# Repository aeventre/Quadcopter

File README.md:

# DIY Quadcopter

A from-scratch DIY quadcopter with a custom-designed flight computer PCB and custom frame CAD. Everything except the ESC and radio module was built from the ground up.

## Overview

This repository contains the KiCad hardware design files for the custom flight controller PCB and the Arduino/PlatformIO firmware that runs on it. The flight controller interfaces a four channel off-the-shelf ESC, an RC receiver via CRSF/ExpressLRS, and an onboard 6-axis IMU to stabilize and control the drone.

## Hardware

### Flight Controller (Custom PCB)

| Component | Part | Role |
|---|---|---|
| MCU | Raspberry Pi Pico (RP2040 / RP2350) | Main processor |
| IMU | LSM6DSO32TR | 6-axis accelerometer + gyroscope (SPI) |
| Power regulator | TPS563200 | 3A synchronous step-down, 4.5–17V in → 3.3V |
| Motor switching | AO3400A MOSFET | N-channel switching |
| Level shifting | BSS138 MOSFET | 3.3V ↔ 5V logic |
| Transient protection | SMAJ14A TVS diode | Input voltage spike protection |

### Interfaces
- **4× ESC connectors** (Motor 1–4) — off-the-shelf 4 channel ESC
- **RC receiver connector** — CRSF/ExpressLRS
- **Electromagnet connector** — payload drop mechanism
- **SPI** — IMU (LSM6DSO32TR on SPI1)
- **USB** — programming and debug via Pico's onboard USB

### Frame & CAD
Custom-designed from scratch (CAD files not included in this repo).

## Firmware

Built with [PlatformIO](https://platformio.org/) targeting the Raspberry Pi Pico using the [earlephilhower Arduino core](https://github.com/earlephilhower/arduino-pico).

### Flight Controller (`Code/Controller_Code/`)

The main flight firmware. Initializes the IMU, ESCs, and CRSF receiver, then runs the control loop.

**Libraries (`lib/`)**

| Library | Description |
|---|---|
| `DroneController` | Core flight controller — PID loop, flight modes, arm/disarm, RAM blackbox |
| `ImuLSM6` | SPI driver for the LSM6DSO32TR (gyro + accel reads) |
| `MotorLib` | PWM motor control via the Servo library (1000–2000 µs) |

**Flight modes**

- **Acro** — pure rate mode; stick input maps directly to roll/pitch/yaw rate setpoints fed into the inner PID loop
- **Balance** — self-leveling; an outer angle P+I loop computes rate setpoints from stick-commanded angles, which the inner rate PID tracks

**Control loop**

```
RC input (CRSF)
    │
    ├─ [Balance mode] Angle P+I → rate setpoint
    │
    └─ Rate PID (roll / pitch / yaw)
           │   gyro LP filter (α = 0.70)
           │   complementary filter for attitude (α = 0.98)
           ▼
       Motor mixer → 4× PWM ESC outputs
```

**RAM blackbox**

Up to 3000 samples are logged to RAM during flight (timestamp, RC inputs, rate commands, gyro rates, PID outputs, motor values, attitude angles). On disarm the log dumps over USB serial as CSV for offline analysis.

### Test Projects

| Project | Description |
|---|---|
| `Code/ELRS_Test/` | Standalone CRSF/ExpressLRS receiver test |
| `Code/ESC_Test/` | ESC test using DShot600 (bit-banged on Pico's second core at 2 kHz) |
| `Code/IMU_test/` | Standalone LSM6DSO32TR read/print test |

### Flight Analysis (`Code/Flight_Analysis/`)

MATLAB script (`PID_Analysis.m`) for post-flight analysis of blackbox CSV logs. Plots RC inputs, commanded vs. measured rates, rate errors, motor outputs, and estimated attitude. 103 flight logs are included.

## Repository Structure

```
Quadcopter/
├── Flight_Controller/
│   ├── Flight_Controller.kicad_pro
│   ├── Flight_Controller.kicad_sch
│   └── Flight_Controller.kicad_pcb
└── Code/
    ├── Controller_Code/          # Main flight firmware (PlatformIO)
    │   ├── src/main.cpp
    │   ├── lib/
    │   │   ├── DroneController/  # Flight controller, PID, blackbox
    │   │   ├── ImuLSM6/          # LSM6DSO32TR SPI driver
    │   │   └── MotorLib/         # PWM ESC control
    │   └── Tests/                # Component test sketches
    ├── ELRS_Test/                # ExpressLRS receiver test
    ├── ESC_Test/                 # DShot600 ESC test
    │   └── lib/DshotLib/         # DShot600 driver (dual-core)
    ├── IMU_test/                 # IMU read test
    └── Flight_Analysis/
        ├── PID_Analysis.m        # MATLAB blackbox analysis script
        └── flight_log_*.csv      # Captured flight logs (103 flights)
```

## Getting Started

### Hardware (KiCad)
1. Install [KiCad 7.x or later](https://www.kicad.org/download/)
2. Clone this repository:
   ```bash
   git clone https://github.com/alecv2211/Quadcopter.git
   ```
3. Open `Flight_Controller/Flight_Controller.kicad_pro`

### Firmware (PlatformIO)
1. Install [PlatformIO](https://platformio.org/install)
2. Open `Code/Controller_Code/` in VS Code with the PlatformIO extension
3. Connect the Pico via USB and run **Upload**

## License

Licensed under the [Apache License 2.0](LICENSE).

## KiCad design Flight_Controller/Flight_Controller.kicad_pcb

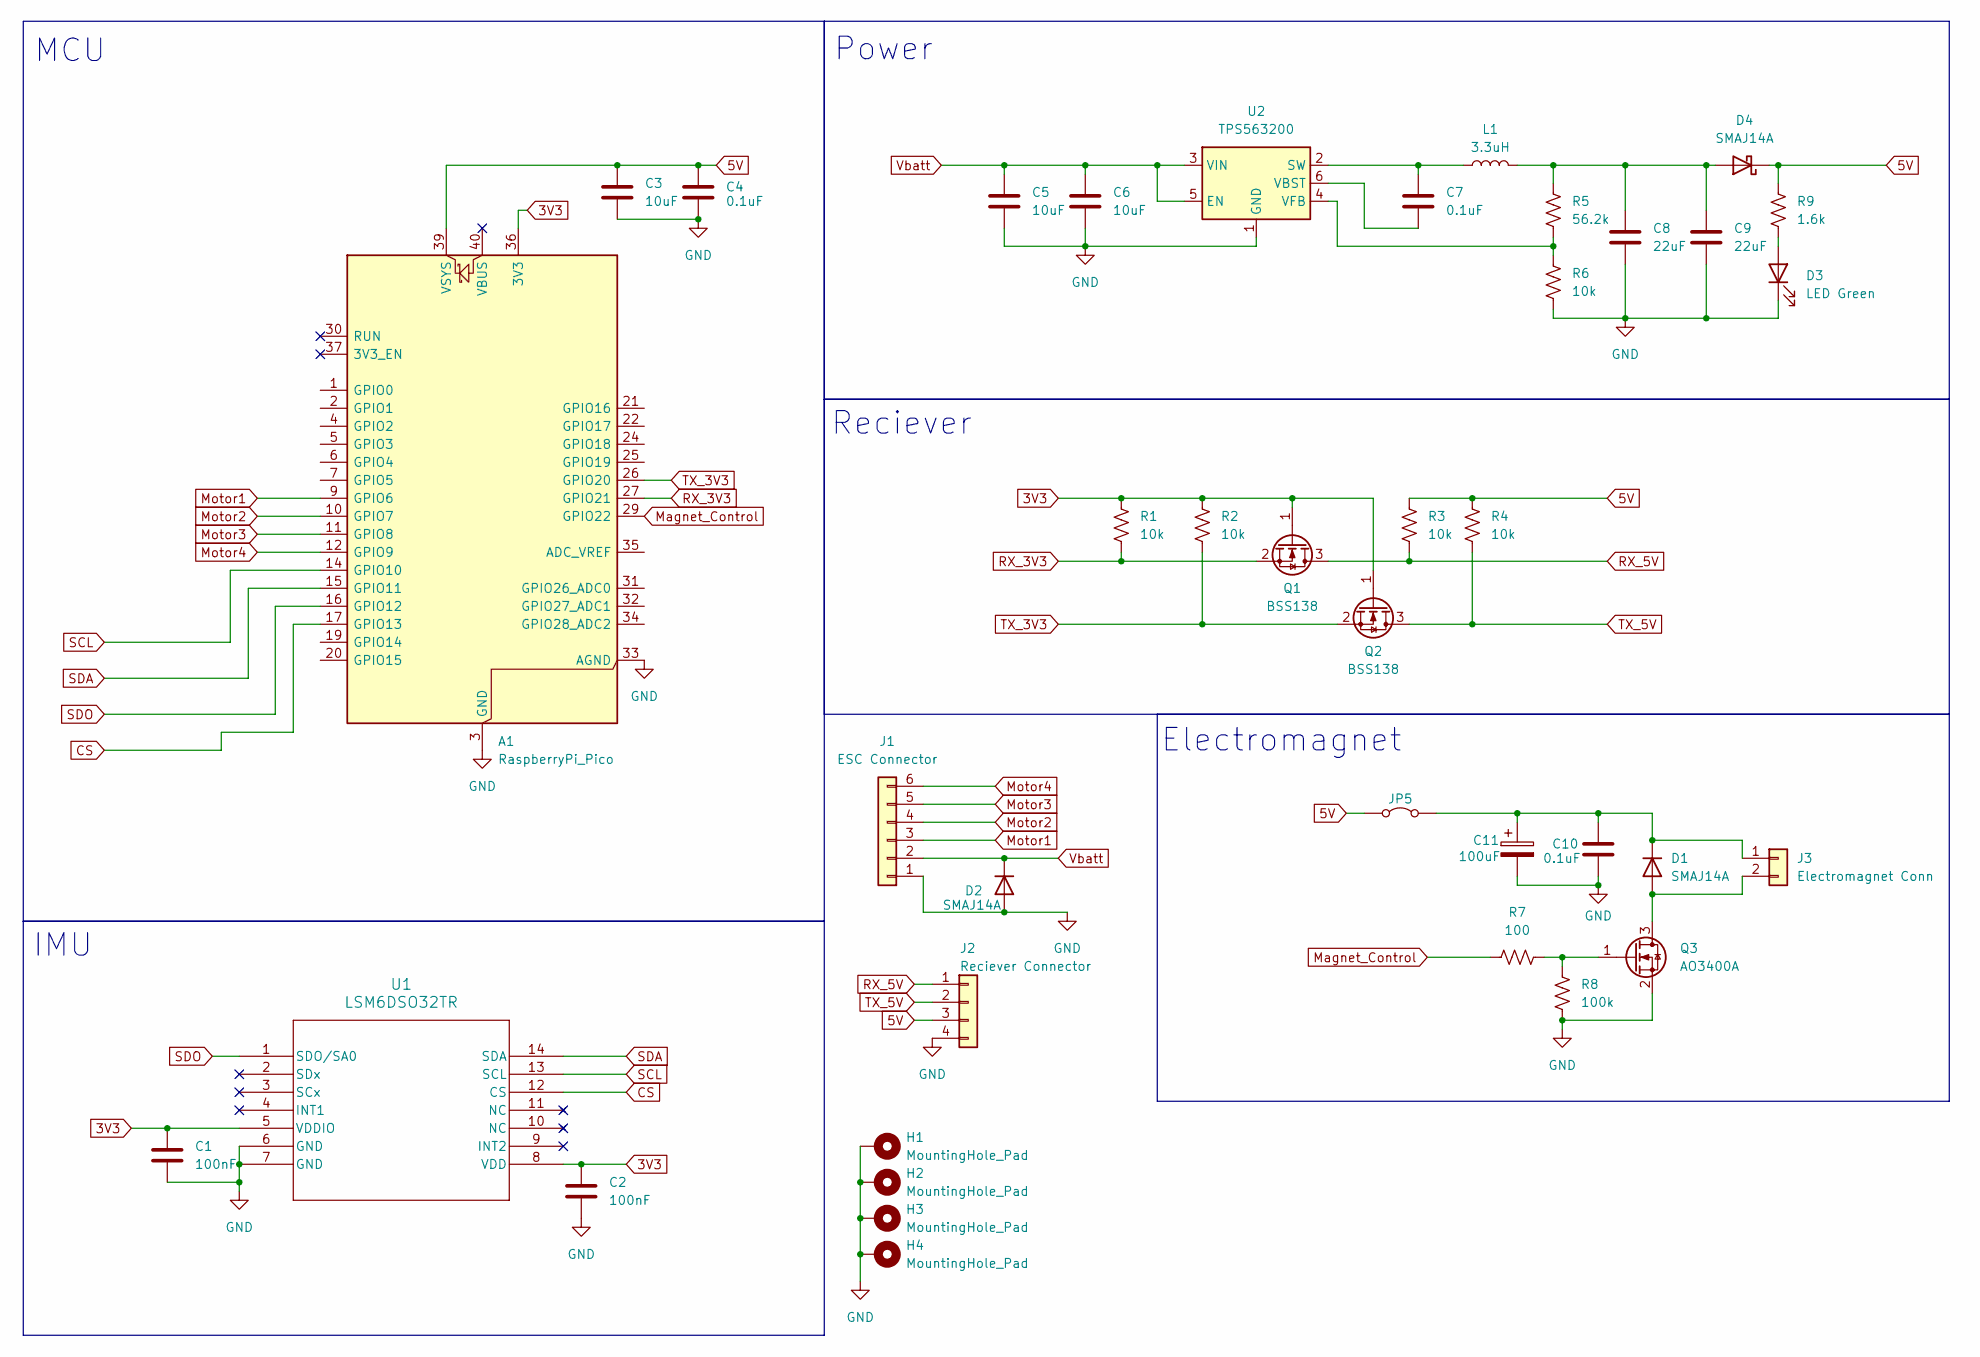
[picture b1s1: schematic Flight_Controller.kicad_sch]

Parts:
A1: RaspberryPi_Pico; RaspberryPi_Pico_Common_SMD
C1, C2: 100nF; C_0603_1608Metric_Pad1.08x0.95mm_HandSolder
C3: 10uF; C_0603_1608Metric_Pad1.08x0.95mm_HandSolder; Digikey Part Number 399-C0805C106K4PACTUCT-ND
C4: 0.1uF; C_0603_1608Metric_Pad1.08x0.95mm_HandSolder; Digikey Part Number 399-C0805C104M5UACTUCT-ND
C5, C6: 10uF; C_0603_1608Metric_Pad1.08x0.95mm_HandSolder
C7, C10: 0.1uF; C_0603_1608Metric_Pad1.08x0.95mm_HandSolder
C8, C9: 22uF; C_0603_1608Metric_Pad1.08x0.95mm_HandSolder
C11: 100uF; C_0603_1608Metric_Pad1.08x0.95mm_HandSolder
D1, D2, D4: SMAJ14A; D_SMA_Handsoldering
D3: LED Green; D_0603_1608Metric_Pad1.05x0.95mm_HandSolder
H1, H2, H3, H4: MountingHole_Pad; MountingHole_3.5mm_Pad
J1: ESC Connector; SolderWire-0.15sqmm_1x06_P4mm_D0.5mm_OD1.5mm_Relief
J2: Reciever Connector; Reciever_Module
J3: Electromagnet Conn; SolderWire-0.15sqmm_1x02_P4mm_D0.5mm_OD1.5mm_Relief
JP5: Jumper_2_Bridged; SolderJumper-2_P1.3mm_Open_TrianglePad1.0x1.5mm
L1: 3.3uH; L_Bourns-SRN8040_8x8.15mm
Q1, Q2: BSS138; SOT-23_Handsoldering
Q3: AO3400A; SOT-23
R1, R2, R3, R4: 10k; R_0603_1608Metric_Pad0.98x0.95mm_HandSolder; PART-NUMBER CPF0603F10KC1
R5: 56.2k; R_0603_1608Metric_Pad0.98x0.95mm_HandSolder
R6: 10k; R_0603_1608Metric_Pad0.98x0.95mm_HandSolder
R7: 100; R_0603_1608Metric_Pad0.98x0.95mm_HandSolder; PART-NUMBER CPF0603F10KC1
R8: 100k; R_0603_1608Metric_Pad0.98x0.95mm_HandSolder; PART-NUMBER CPF0603F10KC1
R9: 1.6k; R_0603_1608Metric_Pad0.98x0.95mm_HandSolder
U1: LSM6DSO32TR; LGA-14_3x2.5mm_P0.5mm_LayoutBorder3x4y; PART-NUMBER 497-LSM6DSO32CT-ND
U2: TPS563200; SOT-23-6

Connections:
3V3: A1.36 (3V3), C1.1, C2.1, Q1.1 (G), Q2.1 (G), R1.1, R2.1, U1.5 (VDDIO), U1.8 (VDD)
5V: A1.39 (VSYS), C3.1, C4.1, D4.1 (K), J2.3, JP5.1 (A), R3.1, R4.1, R9.1
CS: A1.17 (GPIO13), U1.12 (CS)
GND: A1.3 (GND), A1.8 (GND), A1.13 (GND), A1.18 (GND), A1.23 (GND), A1.28 (GND), A1.33 (AGND), A1.38 (GND), C1.2, C2.2, C3.2, C4.2, C5.2, C6.2, C8.2, C9.2, C10.2, C11.2, D2.2 (A), D3.1 (K), H1.1, H2.1, H3.1, H4.1, J1.1, J2.4, Q3.2 (S), R6.2, R8.1, U1.6 (GND), U1.7 (GND), U2.1 (GND)
Magnet_Control: A1.29 (GPIO22), R7.1
Motor1: A1.9 (GPIO6), J1.3
Motor2: A1.10 (GPIO7), J1.4
Motor3: A1.11 (GPIO8), J1.5
Motor4: A1.12 (GPIO9), J1.6
unnamed: D1.2 (A), J3.2, Q3.3 (D)
unnamed: C10.1, C11.1, D1.1 (K), J3.1, JP5.2 (B)
unnamed: D3.2 (A), R9.2
unnamed: C8.1, C9.1, D4.2 (A), L1.2, R5.1
unnamed: Q3.1 (G), R7.2, R8.2
unnamed: C7.1, L1.1, U2.2 (SW)
unnamed: C7.2, U2.6 (VBST)
unnamed: R5.2, R6.1, U2.4 (VFB)
RX_3V3: A1.27 (GPIO21), Q1.2 (S), R1.2
RX_5V: J2.1, Q1.3 (D), R3.2
SCL: A1.14 (GPIO10), U1.13 (SCL)
SDA: A1.15 (GPIO11), U1.14 (SDA)
SDO: A1.16 (GPIO12), U1.1 (SDO/SA0)
TX_3V3: A1.26 (GPIO20), Q2.2 (S), R2.2
TX_5V: J2.2, Q2.3 (D), R4.2
Vbatt: C5.1, C6.1, D2.1 (K), J1.2, U2.3 (VIN), U2.5 (EN)

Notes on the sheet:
MCU
IMU
Power
Reciever
Electromagnet

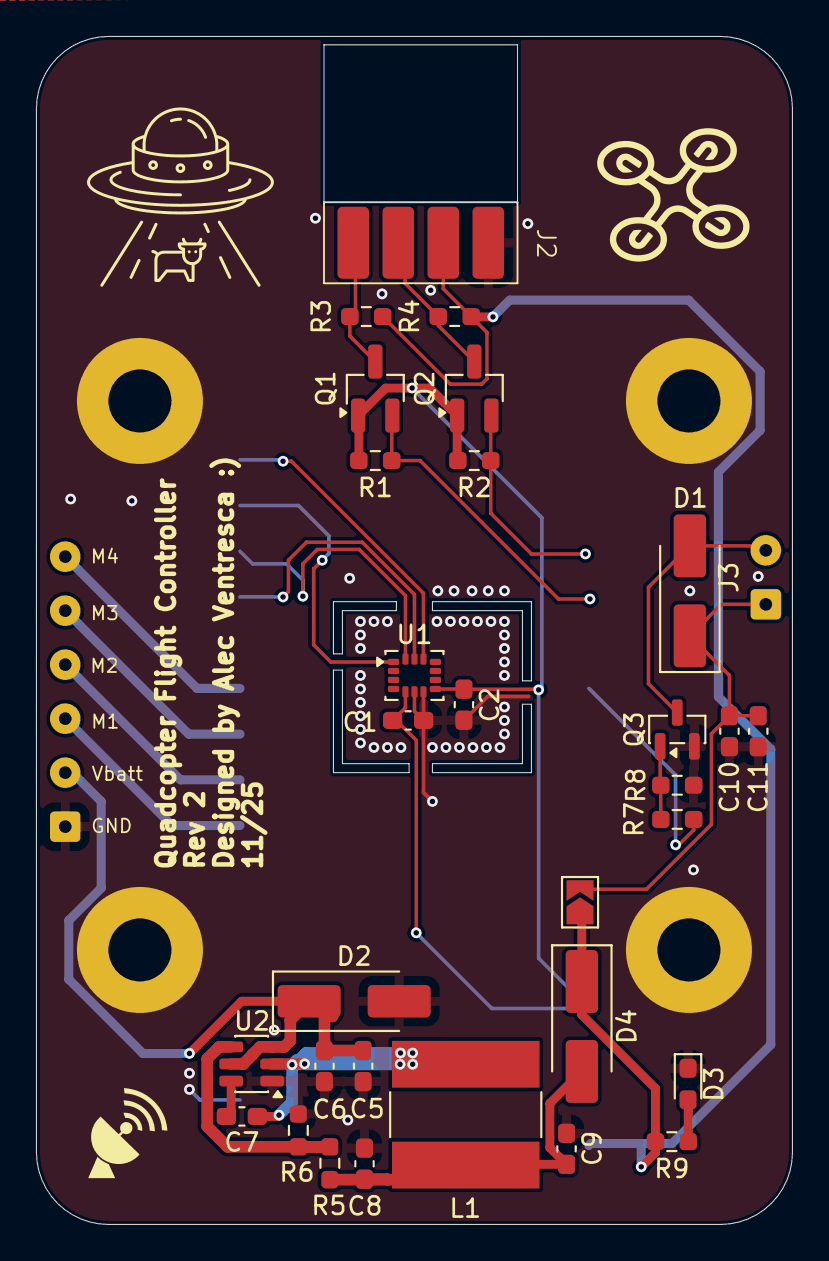
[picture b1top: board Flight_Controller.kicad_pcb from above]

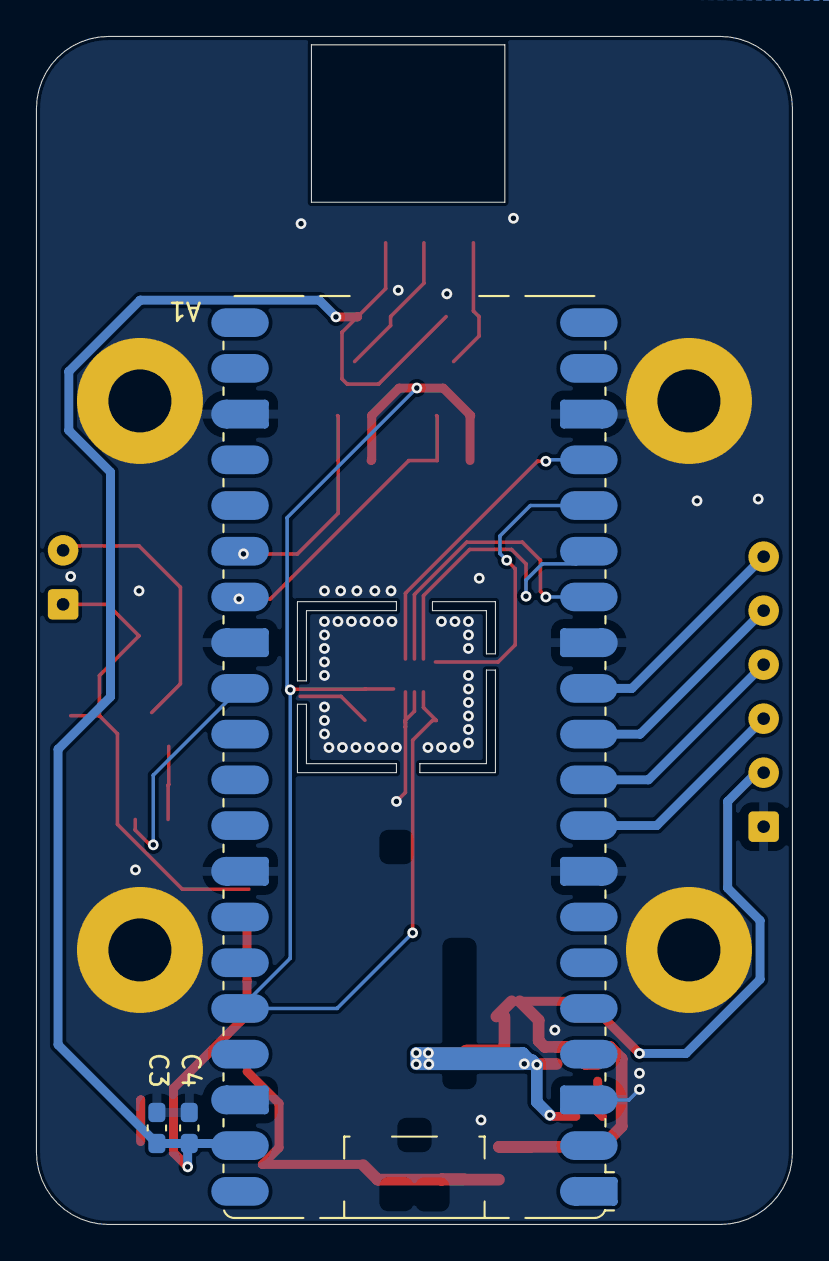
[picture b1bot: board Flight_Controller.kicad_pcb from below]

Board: 2 copper layers, 42.0 x 66.0 mm, 39 parts (3 on the bottom side), 25 nets.

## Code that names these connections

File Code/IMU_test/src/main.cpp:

#include <Arduino.h>
#include <SPI.h>

// ==== Pin + register defs ====
#define CS_PIN    13      // GPIO13 → IMU CS

// LSM6DSO32 registers
#define WHO_AM_I  0x0F
#define CTRL1_XL  0x10
#define CTRL2_G   0x11
#define CTRL3_C   0x12
#define OUTX_L_G  0x22    // start of gyro data (6 bytes)
#define OUTX_L_A  0x28    // start of accel data (6 bytes)

// Expected WHO_AM_I value
#define WHO_VAL   0x6C

// ---- Sensitivities ----
// Treat accel as ±2g for scaling:
// ±2g : 0.061 mg/LSB → 0.000061 g/LSB
const float ACC_SENS = 0.000244f;    // g/LSB

// Gyro: ±250 dps → 8.75 mdps/LSB → 0.00875 dps/LSB
const float GYRO_SENS_250 = 0.00875f;    // dps/LSB

// One SPI config for all IMU transactions
SPISettings imuSPI(1000000, MSBFIRST, SPI_MODE3);

// ==== Low-level SPI helpers ====
uint8_t imuReadReg(uint8_t reg)
{
  uint8_t v;

  digitalWrite(CS_PIN, LOW);
  SPI1.beginTransaction(imuSPI);
  SPI1.transfer(reg | 0x80);   // MSB=1 → read
  v = SPI1.transfer(0x00);
  SPI1.endTransaction();
  digitalWrite(CS_PIN, HIGH);

  return v;
}

void imuWriteReg(uint8_t reg, uint8_t val)
{
  digitalWrite(CS_PIN, LOW);
  SPI1.beginTransaction(imuSPI);
  SPI1.transfer(reg & 0x7F);   // MSB=0 → write
  SPI1.transfer(val);
  SPI1.endTransaction();
  digitalWrite(CS_PIN, HIGH);
}

// ==== High-level IMU helpers ====

// Burst-read gyro + accel in one go (12 bytes)
void imuReadGyroAccel(float &gx, float &gy, float &gz,
                      float &ax, float &ay, float &az)
{
  uint8_t buf[12];

  digitalWrite(CS_PIN, LOW);
  SPI1.beginTransaction(imuSPI);
  // Start at OUTX_L_G, auto-increment will step through all 6 gyro + 6 accel bytes
  SPI1.transfer(OUTX_L_G | 0x80);

  for (int i = 0; i < 12; i++) {
    buf[i] = SPI1.transfer(0x00);
  }

  SPI1.endTransaction();
  digitalWrite(CS_PIN, HIGH);

  // Raw little-endian 16-bit values
  int16_t gx_raw = (int16_t)((buf[1]  << 8) | buf[0]);
  int16_t gy_raw = (int16_t)((buf[3]  << 8) | buf[2]);
  int16_t gz_raw = (int16_t)((buf[5]  << 8) | buf[4]);
  int16_t ax_raw = (int16_t)((buf[7]  << 8) | buf[6]);
  int16_t ay_raw = (int16_t)((buf[9]  << 8) | buf[8]);
  int16_t az_raw = (int16_t)((buf[11] << 8) | buf[10]);

  // Convert to physical units
  gx = gx_raw * GYRO_SENS_250;
  gy = gy_raw * GYRO_SENS_250;
  gz = gz_raw * GYRO_SENS_250;

  ax = ax_raw * ACC_SENS;
  ay = ay_raw * ACC_SENS;
  az = az_raw * ACC_SENS;
}

void imuInit()
{
  // CTRL3_C: BDU=1 (block data update), IF_INC=1 (auto-increment)
  // 0b0100_0100 = 0x44
  imuWriteReg(CTRL3_C, 0x44);
  delay(50);   // give it a moment to latch

  // CTRL1_XL: ODR_XL = 104 Hz (0100 << 4 = 0x40)
  // We'll *ask* for ±4g (0x48), but even if FS bits don't stick,
  // our scale constant is now based on what we actually observe.
  imuWriteReg(CTRL1_XL, 0x48);

  // CTRL2_G (gyro):
  // ODR_G  = 104 Hz → 0b0100 << 4 = 0x40
  // FS_G   = 250 dps (00 in bits [3:2])
  // Final: 0x40
  imuWriteReg(CTRL2_G, 0x40);

  delay(20);

  // Read back to confirm (for debugging / curiosity)
  uint8_t c1 = imuReadReg(CTRL1_XL);
  uint8_t c2 = imuReadReg(CTRL2_G);
  uint8_t c3 = imuReadReg(CTRL3_C);

  Serial.print("CTRL1_XL = 0x"); Serial.println(c1, HEX);
  Serial.print("CTRL2_G  = 0x"); Serial.println(c2, HEX);
  Serial.print("CTRL3_C  = 0x"); Serial.println(c3, HEX);
}

void setup()
{
  Serial.begin(115200);
  delay(2000);

  Serial.println("\n=== LSM6DSO32 SPI Gyro+Accel Test (2g scaling) ===");

  // Configure SPI1 pins to match your PCB routing
  SPI1.setSCK(10);   // GPIO10 → SCK
  SPI1.setTX(11);    // GPIO11 → MOSI
  SPI1.setRX(12);    // GPIO12 → MISO
  SPI1.begin();

  pinMode(CS_PIN, OUTPUT);
  digitalWrite(CS_PIN, HIGH);

  // WHO_AM_I sanity check
  uint8_t who = imuReadReg(WHO_AM_I);
  Serial.print("WHO_AM_I = 0x");
  Serial.println(who, HEX);

  if (who != WHO_VAL) {
    Serial.println("WARNING: IMU WHO_AM_I mismatch (expected 0x6C).");
  }

  imuInit();
  Serial.println("IMU init done (scaled as ±2g, ±250 dps @ 104 Hz).");
}

void loop()
{
  float gx, gy, gz;
  float ax, ay, az;

  imuReadGyroAccel(gx, gy, gz, ax, ay, az);

  Serial.print("ACC [g]   ");
  Serial.print(ax, 3); Serial.print("   ");
  Serial.print(ay, 3); Serial.print("   ");
  Serial.print(az, 3); Serial.print("   |   ");

  Serial.print("GYR [dps] ");
  Serial.print(gx, 2); Serial.print("   ");
  Serial.print(gy, 2); Serial.print("   ");
  Serial.print(gz, 2); Serial.println();

  

  delay(50);   // ~20 Hz print
}

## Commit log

2025-11-01 Prepared sheets for each component
2025-11-01 Change folder name
2025-11-02 add stm32
2025-11-21 Rev 2 PCB done
2026-05-06 Add project README for public GitHub
2026-05-06 Update README with hardware details from schematic
2026-05-06 Add firmware source, test projects, flight analysis data, and update .gitignore
2026-05-06 Update README with firmware architecture and code structure
